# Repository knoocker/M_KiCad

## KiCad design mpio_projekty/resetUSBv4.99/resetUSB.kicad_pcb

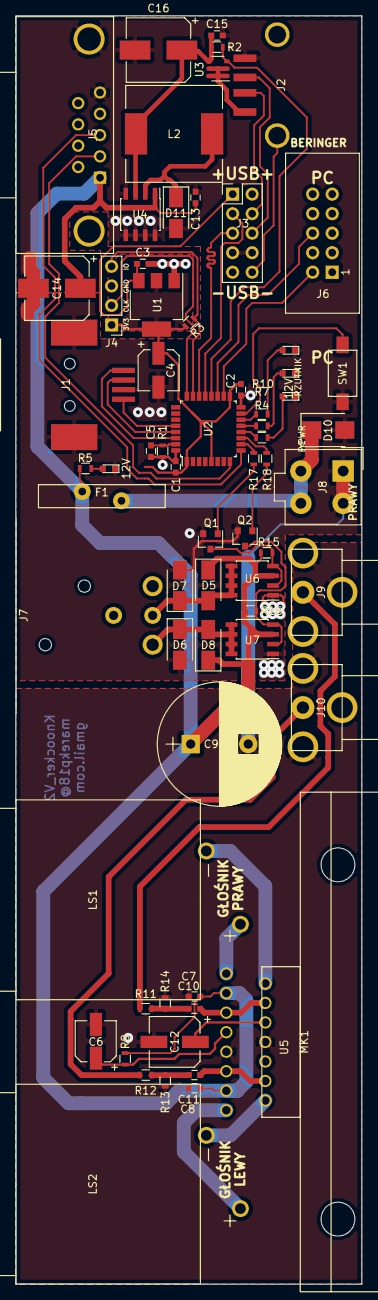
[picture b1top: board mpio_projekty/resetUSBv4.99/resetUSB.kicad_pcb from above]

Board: 2 copper layers, 45.0 x 165.0 mm, 67 parts (0 on the bottom side), 52 nets.

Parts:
C1, C2, C3, C5, C7, C8, C13, C15: 100n; C_0603
C4, C6: 10u; CP_Elec_5x5.3
C9: 4700u; CP_Radial_D16.0mm_P7.50mm
C10, C11: 0.47u; C_0603
C12: 47u; CP_Elec_6.3x5.3
C14, C16: 220u; CP_Elec_8x10.5
D1, D9: RED; LED_0603
D2: GREEN; LED_0603
D3: BLUE; LED_0603
D5, D6, D7, D8: US1D; D_SMA
D10: transil_15V; D_SMB
D11: SS14; D_SMA
F1: RG700-16; RG10A-16
J1: USBB-G-SMD; USB-B_SMD
J2: TUEA4F2SOBHT; USB-A_SMD
J3: Conn_02x05; Pin_Header_Straight_2x05_Pitch2.54mm
J4: SWD_4pin; Pin_Header_Straight_1x04_Pitch2.54mm
J5: DE09-SL-24; DSUB-9
J6: Conn_02x05; IDC10
J7: AC3MAH-AU-PRE
J8: Mini-Fit Jr; 4,2mm; Molex_MiniFit-JR-5556-04A_2x02x4.20mm_Straight
J9, J10: FC68391
L2: 47u; L_12x12mm_h6mm
LS1, LS2: NLJ2MD-H
MK1: SK48-50-SA-3
Q1, Q2: BC817; SOT-23
R1, R2, R3, R5: 100K; R_0603
R4: 22K; R_0603
R7: 6K8; R_0603
R9: 47K; R_0603
R10: 33K; R_0603
R11, R12: 4K7; R_0603
R13, R14, R15, R16, R17, R18: 10K; R_0603
SW1: TACTM-34N-F; SW_3x6_1,6x7,4
U1: LD1117S33TR; SOT-223-3_TabPin2
U2: STM32F042K6Tx; LQFP-32_7x7mm_Pitch0.8mm
U3: IRLTS2242; TSOP-6_1.65x3.05mm_Pitch0.95mm
U4: AP1509-50SG-13; SOIC-8_3.9x4.9mm_Pitch1.27mm
U5: TDA7375; MULTIWATT15
U6, U7: AO4616; SOIC-8_3.9x4.9mm_Pitch1.27mm

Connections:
+3V3: C1.1, C2.1, C4.1, J4.1, R3.2, U1.2, U2.1, U2.5, U2.17
+5P: C3.1, J3.1, U1.3
+5V: C15.1, C16.1, L2.2, R2.1, U3.4, U4.3
+12V: C7.1, C8.1, C9.1, C13.1, C14.1, D5.1, D6.1, F1.2, J5.1, R5.1, R9.1, R15.2, R16.2, U4.1, U5.3, U5.13, U6.3, U7.3
/LED_BLUE: R10.2, U2.14
/LED_GREEN: R7.2, U2.13
/LED_RED: R4.2, U2.12
/M_IN1: R17.2, U2.10
/M_IN2: R18.2, U2.11
/PC_LED: J6.2, U2.18
/PC_PWR: J6.6, U2.19
/PRZYCISK: SW1.2, U2.15
/RX: J5.3, U2.9
/RZUTNIK_DM: J1.2, U2.29
/RZUTNIK_DP: J1.3, U2.30
/RZUTNIK_VBUS: J1.1, U2.28
/SWCLK: J4.2, U2.24
/SWDIO: J4.4, R3.1, U2.23
/TX: J5.2, U2.8
/USB_DM: J3.3, U2.21
/USB_DP: J3.5, U2.22
/USB_PWR: R2.2, U2.20, U3.3
GND: C1.2, C2.2, C3.2, C4.2, C5.2, C6.2, C7.2, C8.2, C9.2, C12.2, C13.2, C14.2, C15.2, C16.2, D1.1, D2.1, D3.1, D7.2, D8.2, D9.1, D10.2, D11.2, J1.4, J1.5, J2.4, J3.7, J3.8, J4.3, J5.0, J5.5, J8.1, J8.2, J9.2, J10.2, Q1.2, Q2.2, R1.1, R13.2, R14.2, SW1.1, U1.1, U2.16, U2.32, U4.4, U4.5, U4.6, U4.7, U4.8, U5.8, U5.9, U6.1, U7.1
unnamed: C5.1, R1.2, U2.31
unnamed: C6.1, R9.2, U5.7
unnamed: C10.1, R11.2, R14.1
unnamed: C10.2, U5.4, U5.5
unnamed: C11.1, R12.2, R13.1
unnamed: C11.2, U5.11, U5.12
unnamed: C12.1, U5.6
unnamed: D1.2, R4.1
unnamed: D2.2, R7.1
unnamed: D3.2, R10.1
unnamed: D5.2, D7.1, J7.3, U6.5, U6.6, U6.7, U6.8
unnamed: D6.2, D8.1, J7.2, U7.5, U7.6, U7.7, U7.8
unnamed: D9.2, R5.2
unnamed: D10.1, F1.1, J8.3, J8.4
unnamed: D11.1, L2.1, U4.2
unnamed: J2.1, U3.1, U3.2, U3.5, U3.6
unnamed: J2.2, J3.4
unnamed: J2.3, J3.6
unnamed: J2.5, J3.10
unnamed: J9.1, R11.1
unnamed: J10.1, R12.1
unnamed: LS1.1, U5.1
unnamed: LS1.2, U5.2
unnamed: LS2.1, U5.15
unnamed: LS2.2, U5.14
unnamed: Q1.1, R17.1
unnamed: Q1.3, R15.1, U6.2, U6.4
unnamed: Q2.1, R18.1
unnamed: Q2.3, R16.1, U7.2, U7.4

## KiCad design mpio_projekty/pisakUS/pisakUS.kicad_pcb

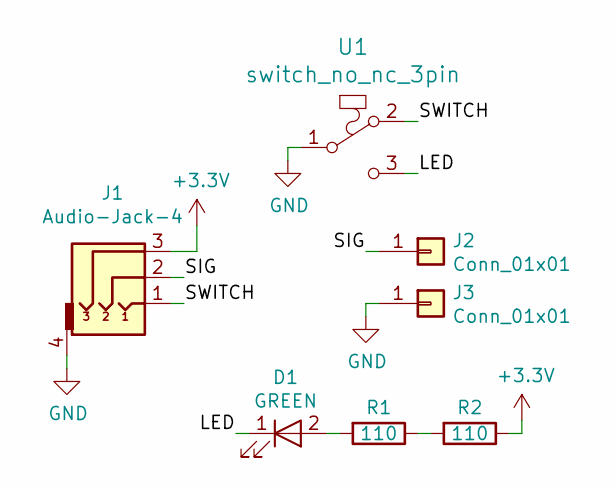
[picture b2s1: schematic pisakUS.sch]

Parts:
D1: GREEN; LED_0603
J1: Audio-Jack-4; 1503_13_VP3
J2, J3: Conn_01x01; Pin_Header_Straight_1x01_Pitch2.54mm
R1, R2: 110; R_0603
U1: switch_no_nc_3pin; D2FS-FL-N-T

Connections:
+3V3: J1.3, R2.1
/LED: D1.1 (K), U1.3
/SIG: J1.2, J2.1
/SWITCH: J1.1, U1.2
GND: J1.4, J3.1, U1.1
unnamed: D1.2 (A), R1.2
unnamed: R1.1, R2.2

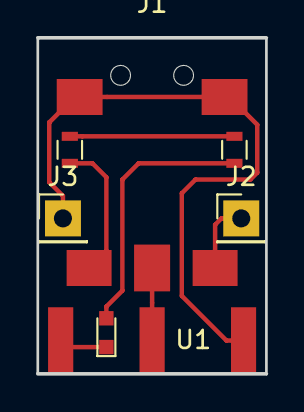
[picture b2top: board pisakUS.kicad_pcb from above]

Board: 2 copper layers, 12.7 x 18.7 mm, 7 parts (0 on the bottom side), 7 nets.

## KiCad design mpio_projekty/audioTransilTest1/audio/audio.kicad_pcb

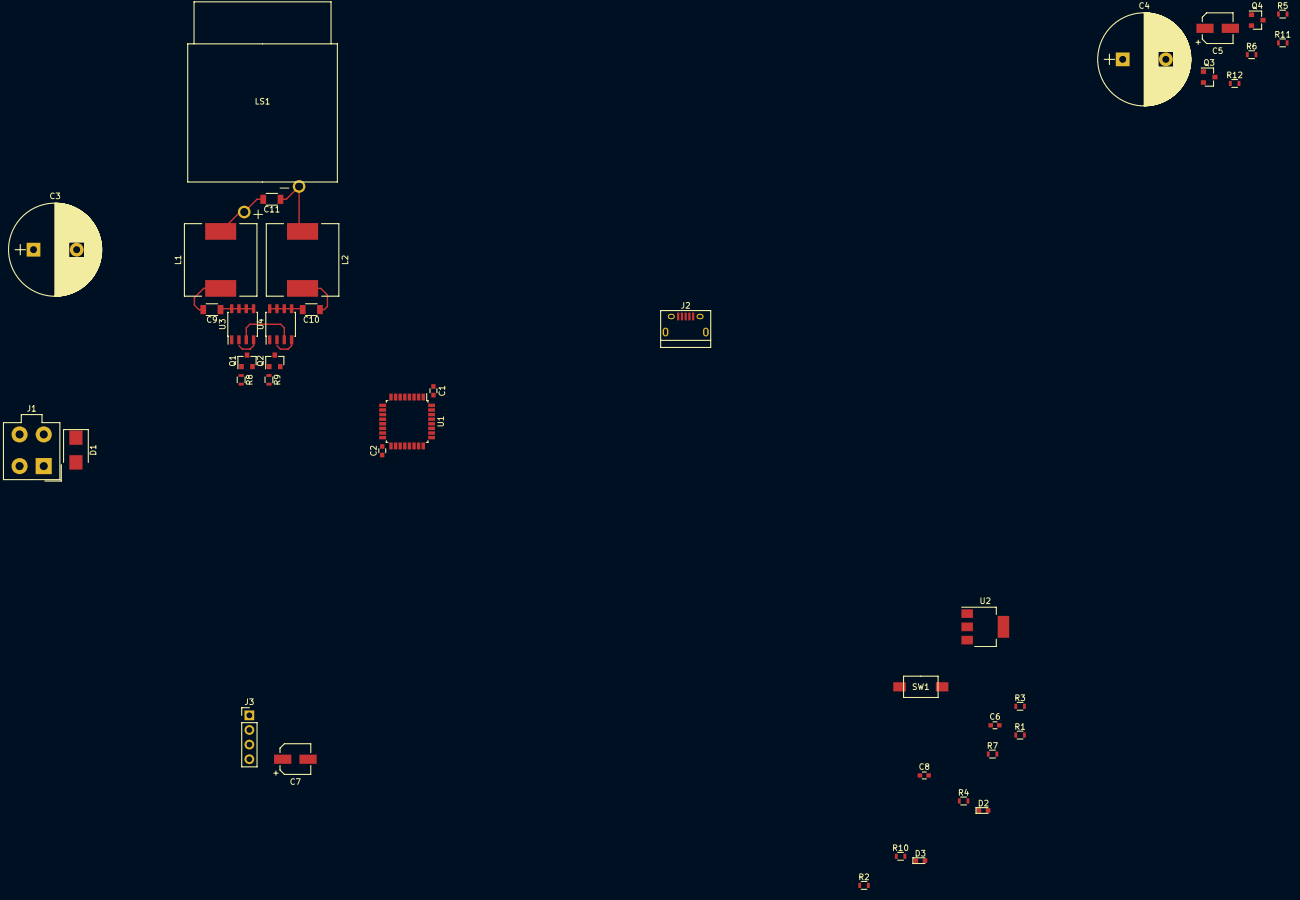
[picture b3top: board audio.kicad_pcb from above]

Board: 2 copper layers, 41 parts (0 on the bottom side), 29 nets.

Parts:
C1, C2, C6, C8: 100n; C_0603
C3: 4700u; CP_Radial_D16.0mm_P7.50mm
C4: 330u; CP_Radial_D16.0mm_P7.50mm
C5, C7: 10u; CP_Elec_5x5.3
C9, C10: 1u; C_1206
C11: 680n; C_1206
D1: transil_15V; D_SMB
D2, D3: RED; LED_0603
J1: Mini-Fit Jr; 4,2mm; Molex_MiniFit-JR-5556-04A_2x02x4.20mm_Straight
J2: USB_B; USB_Micro-B
J3: SWD_4pin; Pin_Header_Straight_1x04_Pitch2.54mm
L1, L2: 10/22u; L_12x12mm_h8mm
LS1: NLJ2MD-H
Q1, Q2, Q3, Q4: BC817; SOT-23
R1, R2, R3: 100K; R_0603
R4, R5, R6, R7, R8, R9, R11, R12: 10K; R_0603
R10: 22K; R_0603
SW1: TACTM-34N-F; SW_3x6_1,6x7,4
U1: STM32F042K6Tx; LQFP-32_7x7mm_Pitch0.8mm
U2: LD1117S33TR; SOT-223-3_TabPin2
U3, U4: AO4616; SOIC-8_3.9x4.9mm_Pitch1.27mm

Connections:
+3V3: C1.1, C2.1, C7.1, J3.1, R3.2, U1.1, U1.5, U1.17, U2.2
+5V: C5.1, C6.1, J2.1, U2.3
+12V: C3.1, C4.1, D1.1, J1.3, J1.4, R1.1, R4.2, R5.2, R6.2, R7.2, U3.3, U4.3
/SWCLK: J3.2, U1.24
/SWDIO: J3.4, R3.1, U1.23
/USB_M: J2.2, U1.21
/USB_P: J2.3, U1.22
/audio_1: R8.2, U1.18
/audio_1N: R11.2, U1.13
/audio_2: R9.2, U1.19
/audio_2N: R12.2, U1.14
GND: C1.2, C2.2, C3.2, C4.2, C5.2, C6.2, C7.2, C8.2, D1.2, D2.1, D3.1, J1.1, J1.2, J2.4, J2.5, J3.3, Q1.2, Q2.2, Q3.2, Q4.2, R2.1, SW1.1, U1.16, U1.32, U2.1, U3.1, U4.1
unnamed: C8.1, R2.2, U1.31
unnamed: C9.1, U3.5, U3.6, U3.7, U3.8
unnamed: C9.2, L1.1
unnamed: C10.1, L2.2
unnamed: C10.2, U4.5, U4.6, U4.7, U4.8
unnamed: C11.1, L2.1, LS1.2
unnamed: C11.2, L1.2, LS1.1
unnamed: D2.2, R1.2
unnamed: D3.2, R10.1
unnamed: Q1.1, R8.1
unnamed: Q1.3, R4.1, U3.4
unnamed: Q2.1, R9.1
unnamed: Q2.3, R7.1, U4.4
unnamed: Q3.1, R11.1
unnamed: Q3.3, R5.1, U3.2
unnamed: Q4.1, R12.1
unnamed: Q4.3, R6.1, U4.2

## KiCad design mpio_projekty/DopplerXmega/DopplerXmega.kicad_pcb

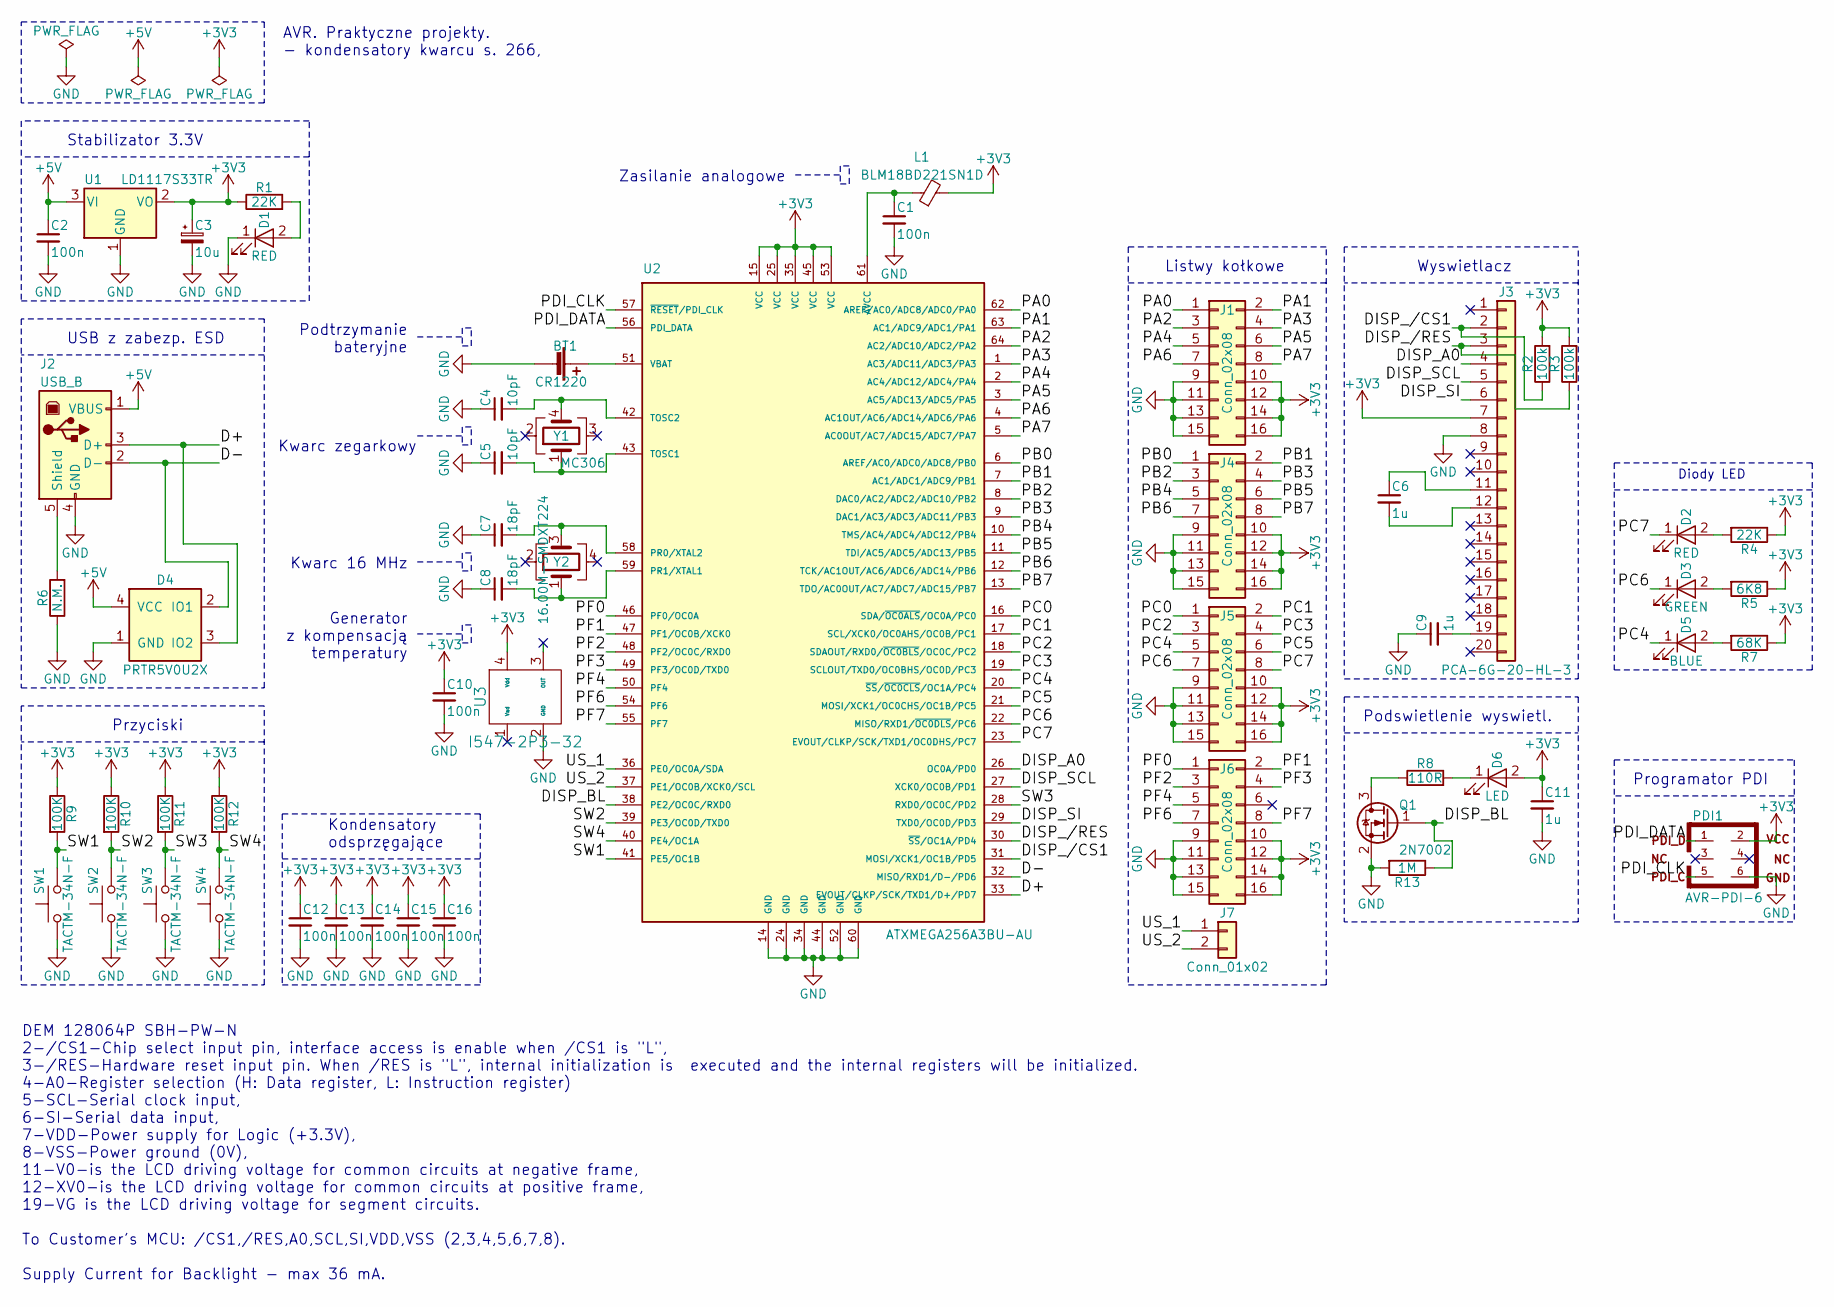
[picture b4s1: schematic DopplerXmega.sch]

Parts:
BT1: CR1220; Keystone_3000_1x12mm-CoinCell
C1, C2, C10, C12, C13, C14, C15, C16: 100n; C_0603
C3: 10u; CP_Elec_5x5.3
C4, C5: 10pF; C_0603
C6, C9, C11: 1u; C_0603
C7, C8: 18pF; C_0603
D1, D2: RED; LED_0603
D3: GREEN; LED_0603
D4: PRTR5V0U2X; SOT-143
D5: BLUE; LED_0603
D6: LED; DEM_128064P_SBH-PW-N
J1, J4, J5, J6: Conn_02x08; Pin_Header_Straight_2x08_Pitch2.54mm
J2: USB_B; USB_Micro-B
J3: PCA-6G-20-HL-3
J7: Conn_01x02; Pin_Header_Straight_1x02_Pitch2.54mm
L1: BLM18BD221SN1D; L_0603
PDI1: AVR-PDI-6; Pin_Header_Straight_2x03_Pitch2.54mm
Q1: 2N7002; SOT-23
R1, R4: 22K; R_0603
R2, R3: 100k; R_0603
R5: 6K8; R_0603
R6: N.M.; R_0603
R7: 68K; R_0603
R8: 110R; R_0603
R9, R10, R11, R12: 100K; R_0603
R13: 1M; R_0603
SW1, SW2, SW3, SW4: TACTM-34N-F; SW_3x6_1,6x7,4
U1: LD1117S33TR; SOT-223-3_TabPin2
U2: ATXMEGA256A3BU-AU; TQFP-64_14x14mm_Pitch0.8mm
U3: I547-2P3-32; crystal_3.2x2.5
Y1: MC306; Crystal_SMD_SeikoEpson_MC306-4pin_8.0x3.2mm
Y2: 16.00M-SMDXT224; Crystal_SMD_2520-4pin_2.5x2.0mm

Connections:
+3V3: C3.1, C10.1, C11.1, C12.1, C13.1, C14.1, C15.1, C16.1, D6.2 (A), J1.10, J1.12, J1.14, J1.16, J3.7, J4.10, J4.12, J4.14, J4.16, J5.10, J5.12, J5.14, J5.16, J6.10, J6.12, J6.14, J6.16, L1.2, PDI1.2, R1.1, R2.2, R3.2, R4.1, R5.1, R7.1, R9.1, R10.1, R11.1, R12.1, U1.2 (VO), U2.15 (VCC), U2.25 (VCC), U2.35 (VCC), U2.45 (VCC), U2.53 (VCC), U3.4 (Vdd)
+5V: C2.1, D4.4 (VCC), J2.1 (VBUS), U1.3 (VI)
/D+: D4.3 (IO2), J2.3 (D+), U2.33 (EVOUT/CLKP/SCK/TXD1/D+/PD7)
/D-: D4.2 (IO1), J2.2 (D-), U2.32 (MISO/RXD1/D-/PD6)
/DISP_/CS1: J3.2, R2.1, U2.31 (MOSI/XCK1/OC1B/PD5)
/DISP_/RES: J3.3, R3.1, U2.30 (~SS~/OC1A/PD4)
/DISP_A0: J3.4, U2.26 (OC0A/PD0)
/DISP_BL: Q1.1 (G), R13.1, U2.38 (PE2/OC0C/RXD0)
/DISP_SCL: J3.5, U2.27 (XCK0/OC0B/PD1)
/DISP_SI: J3.6, U2.29 (TXD0/OC0D/PD3)
/PA0: J1.1, U2.62 (AREF/AC0/ADC8/ADC0/PA0)
/PA1: J1.2, U2.63 (AC1/ADC9/ADC1/PA1)
/PA2: J1.3, U2.64 (AC2/ADC10/ADC2/PA2)
/PA3: J1.4, U2.1 (AC3/ADC11/ADC3/PA3)
/PA4: J1.5, U2.2 (AC4/ADC12/ADC4/PA4)
/PA5: J1.6, U2.3 (AC5/ADC13/ADC5/PA5)
/PA6: J1.7, U2.4 (AC1OUT/AC6/ADC14/ADC6/PA6)
/PA7: J1.8, U2.5 (AC0OUT/AC7/ADC15/ADC7/PA7)
/PB0: J4.1, U2.6 (AREF/AC0/ADC0/ADC8/PB0)
/PB1: J4.2, U2.7 (AC1/ADC1/ADC9/PB1)
/PB2: J4.3, U2.8 (DAC0/AC2/ADC2/ADC10/PB2)
/PB3: J4.4, U2.9 (DAC1/AC3/ADC3/ADC11/PB3)
/PB4: J4.5, U2.10 (TMS/AC4/ADC4/ADC12/PB4)
/PB5: J4.6, U2.11 (TDI/AC5/ADC5/ADC13/PB5)
/PB6: J4.7, U2.12 (TCK/AC1OUT/AC6/ADC6/ADC14/PB6)
/PB7: J4.8, U2.13 (TDO/AC0OUT/AC7/ADC7/ADC15/PB7)
/PC0: J5.1, U2.16 (SDA/~OC0ALS~/OC0A/PC0)
/PC1: J5.2, U2.17 (SCL/XCK0/OC0AHS/OC0B/PC1)
/PC2: J5.3, U2.18 (SDAOUT/RXD0/~OC0BLS~/OC0C/PC2)
/PC3: J5.4, U2.19 (SCLOUT/TXD0/OC0BHS/OC0D/PC3)
/PC4: D5.1 (K), J5.5, U2.20 (~SS~/~OC0CLS~/OC1A/PC4)
/PC5: J5.6, U2.21 (MOSI/XCK1/OC0CHS/OC1B/PC5)
/PC6: D3.1 (K), J5.7, U2.22 (MISO/RXD1/~OC0DLS~/PC6)
/PC7: D2.1 (K), J5.8, U2.23 (EVOUT/CLKP/SCK/TXD1/OC0DHS/PC7)
/PDI_CLK: PDI1.5, U2.57 (~RESET~/PDI_CLK)
/PDI_DATA: PDI1.1, U2.56 (PDI_DATA)
/PF0: J6.1, U2.46 (PF0/OC0A)
/PF1: J6.2, U2.47 (PF1/OC0B/XCK0)
/PF2: J6.3, U2.48 (PF2/OC0C/RXD0)
/PF3: J6.4, U2.49 (PF3/OC0D/TXD0)
/PF4: J6.5, U2.50 (PF4)
/PF6: J6.7, U2.54 (PF6)
/PF7: J6.8, U2.55 (PF7)
/SW1: R9.2, SW1.2, U2.41 (PE5/OC1B)
/SW2: R10.2, SW2.2, U2.39 (PE3/OC0D/TXD0)
/SW3: R11.2, SW3.2, U2.28 (RXD0/OC0C/PD2)
/SW4: R12.2, SW4.2, U2.40 (PE4/OC1A)
/US_1: J7.1, U2.36 (PE0/OC0A/SDA)
/US_2: J7.2, U2.37 (PE1/OC0B/XCK0/SCL)
GND: BT1.2 (-), C1.2, C2.2, C3.2, C4.1, C5.1, C7.1, C8.1, C9.1, C10.2, C11.2, C12.2, C13.2, C14.2, C15.2, C16.2, D1.1 (K), D4.1 (GND), J1.9, J1.11, J1.13, J1.15, J2.4 (GND), J3.8, J4.9, J4.11, J4.13, J4.15, J5.9, J5.11, J5.13, J5.15, J6.9, J6.11, J6.13, J6.15, PDI1.6, Q1.2 (S), R6.1, R13.2, SW1.1, SW2.1, SW3.1, SW4.1, U1.1 (GND), U2.14 (GND), U2.24 (GND), U2.34 (GND), U2.44 (GND), U2.52 (GND), U2.60 (GND), U3.2 (GND)
unnamed: BT1.1 (+), U2.51 (VBAT)
unnamed: C1.1, L1.1, U2.61 (AVCC)
unnamed: C4.2, U2.42 (TOSC2), Y1.4
unnamed: C5.2, U2.43 (TOSC1), Y1.1
unnamed: C6.1, J3.11
unnamed: C6.2, J3.12
unnamed: C7.2, U2.58 (PR0/XTAL2), Y2.3
unnamed: C8.2, U2.59 (PR1/XTAL1), Y2.1
unnamed: C9.2, J3.19
unnamed: D1.2 (A), R1.2
unnamed: D2.2 (A), R4.2
unnamed: D3.2 (A), R5.2
unnamed: D5.2 (A), R7.2
unnamed: D6.1 (K), R8.2
unnamed: J2.5 (Shield), R6.2
unnamed: Q1.3 (D), R8.1

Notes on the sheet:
AVR. Praktyczne projekty. - kondensatory kwarcu s. 266,
Kondensatory odsprzęgające
DEM 128064P SBH-PW-N 2-/CS1-Chip select input pin, interface access is enable when /CS1 is "L", 3-/RES-Hardware reset input pin. When /RES is "L", internal initialization is executed and the internal registers will be initialized. 4-A0-Register selection (H: Data register, L: Instruction register) 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
Programator PDI
Podswietlenie wyswietl.
Wyswietlacz
Listwy kołkowe
Przyciski
USB z zabezp. ESD
Stabilizator 3.3V
Podtrzymanie bateryjne
Kwarc zegarkowy
Kwarc 16 MHz
Generator z kompensacją temperatury
Zasilanie analogowe
Diody LED

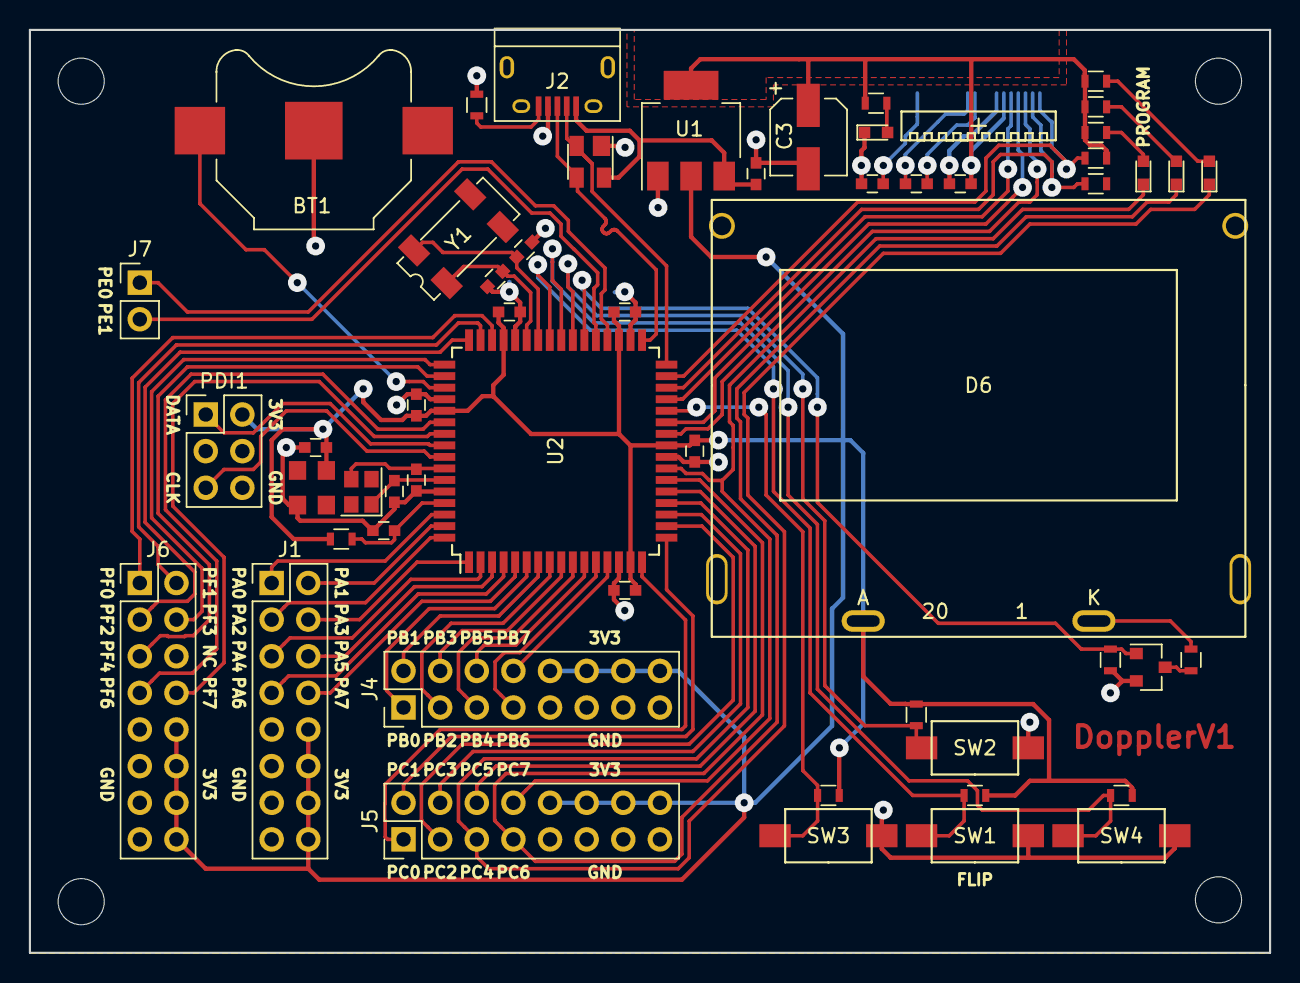
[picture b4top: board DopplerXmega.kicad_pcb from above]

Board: 2 copper layers, 86.0 x 64.0 mm, 55 parts (1 on the bottom side), 66 nets.

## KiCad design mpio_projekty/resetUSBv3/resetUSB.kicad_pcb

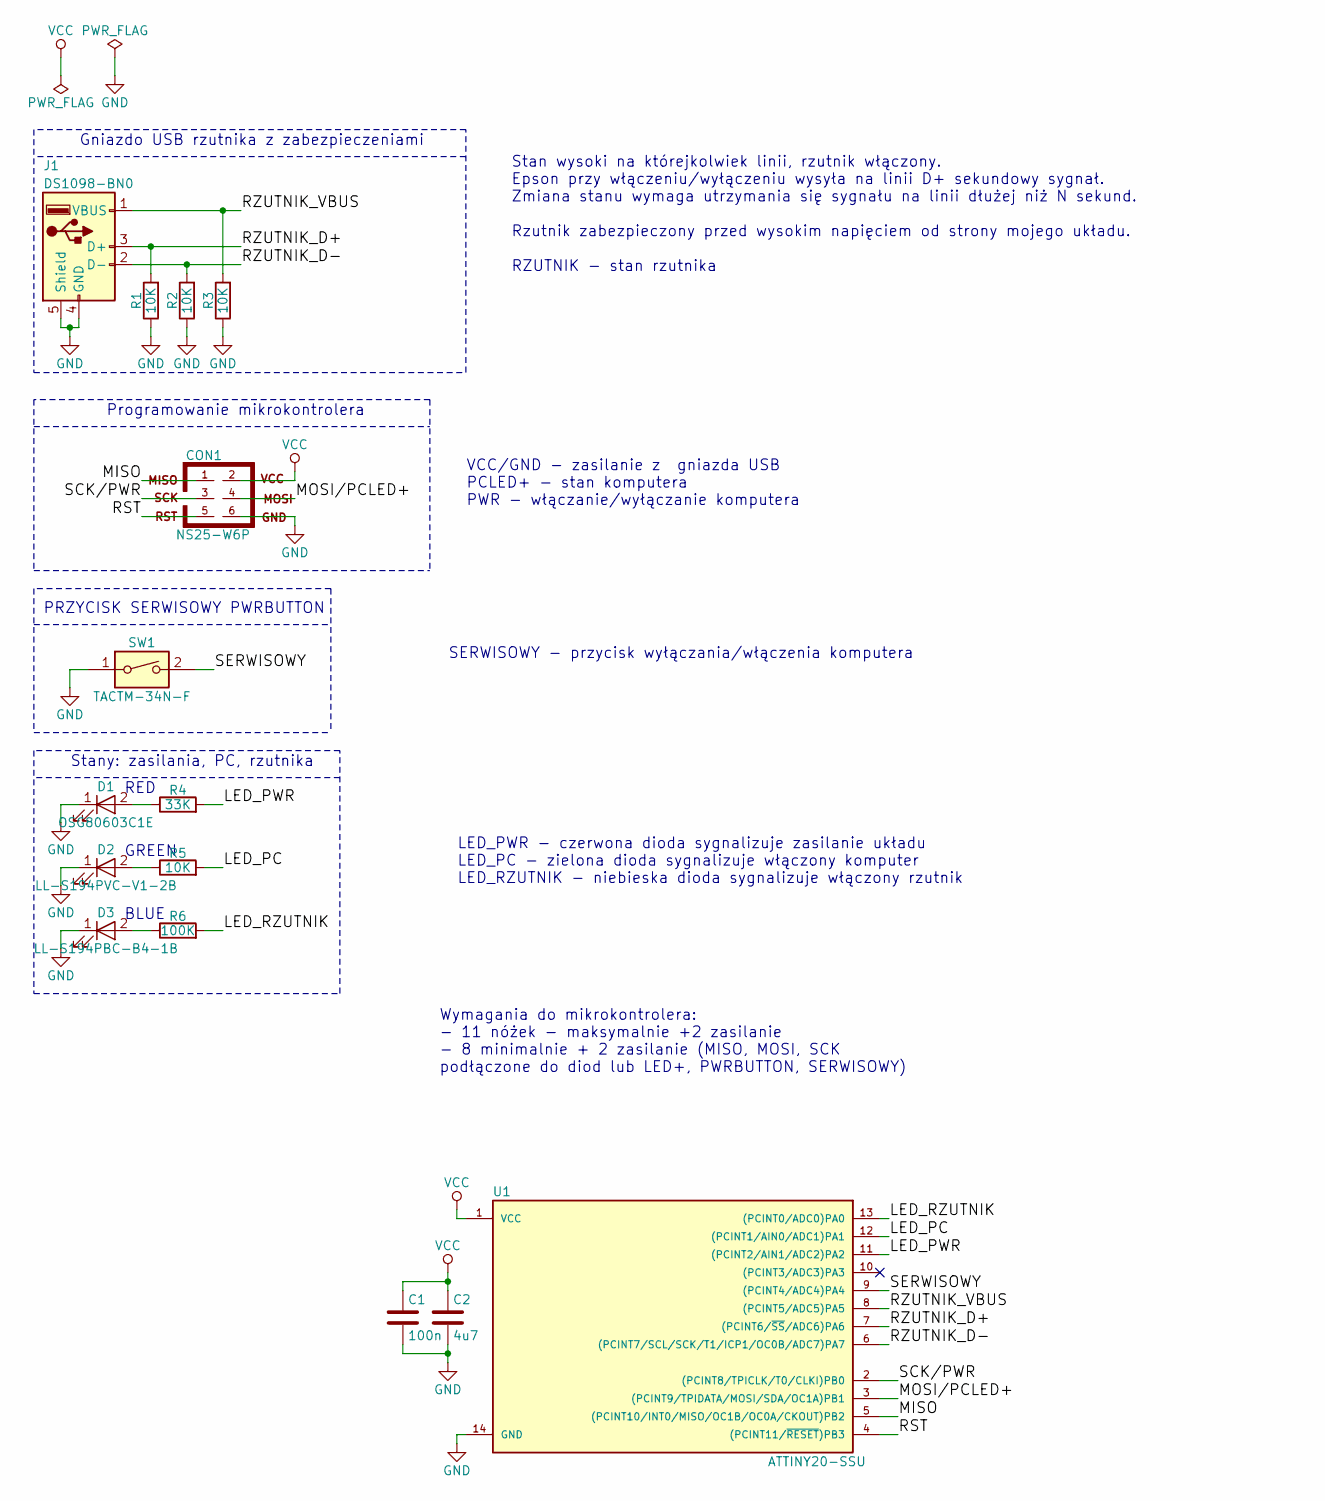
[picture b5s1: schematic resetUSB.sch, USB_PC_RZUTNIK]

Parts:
C1: 100n; C_0805
C2: 4u7; C_0603
CON1: NS25-W6P
D1: OSG80603C1E; LED_0603
D2: LL-S194PVC-V1-2B; LED_0603
D3: LL-S194PBC-B4-1B; LED_0603
J1: DS1098-BN0; USB_A_CONNFLY_DS1098
R1, R2, R3, R5: 10K; R_0603
R4: 33K; R_0603
R6: 100K; R_0603
SW1: TACTM-34N-F; SW_3x6_1,6x7,4
U1: ATTINY20-SSU; SOIC-14_3.9x8.7mm_Pitch1.27mm

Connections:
/LED_PC: R5.2, U1.12 ((PCINT1/AIN0/ADC1)PA1)
/LED_PWR: R4.2, U1.11 ((PCINT2/AIN1/ADC2)PA2)
/LED_RZUTNIK: R6.2, U1.13 ((PCINT0/ADC0)PA0)
/MISO: CON1.1, U1.5 ((PCINT10/INT0/MISO/OC1B/OC0A/CKOUT)PB2)
/MOSI/PCLED+: CON1.4, U1.3 ((PCINT9/TPIDATA/MOSI/SDA/OC1A)PB1)
/RST: CON1.5, U1.4 ((PCINT11/~RESET~)PB3)
/RZUTNIK_D+: J1.3 (D+), R1.2, U1.7 ((PCINT6/~SS~/ADC6)PA6)
/RZUTNIK_D-: J1.2 (D-), R2.2, U1.6 ((PCINT7/SCL/SCK/T1/ICP1/OC0B/ADC7)PA7)
/RZUTNIK_VBUS: J1.1 (VBUS), R3.2, U1.8 ((PCINT5/ADC5)PA5)
/SCK/PWR: CON1.3, U1.2 ((PCINT8/TPICLK/T0/CLKI)PB0)
/SERWISOWY: SW1.2, U1.9 ((PCINT4/ADC4)PA4)
GND: C1.2, C2.2, CON1.6, D1.1 (K), D2.1 (K), D3.1 (K), J1.4 (GND), J1.5 (Shield), R1.1, R2.1, R3.1, SW1.1, U1.14 (GND)
unnamed: D1.2 (A), R4.1
unnamed: D2.2 (A), R5.1
unnamed: D3.2 (A), R6.1
VCC: C1.1, C2.1, CON1.2, U1.1 (VCC)

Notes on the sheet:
Gniazdo USB rzutnika z zabezpieczeniami
Stan wysoki na którejkolwiek linii, rzutnik włączony. Epson przy włączeniu/wyłączeniu wysyła na linii D+ sekundowy sygnał. Zmiana stanu wymaga utrzymania się sygnału na linii dłużej niż N sekund. Rzutnik zabezpieczony przed wysokim napięciem od strony mojego układu. RZUTNIK - stan rzutnika
VCC/GND - zasilanie z gniazda USB PCLED+ - stan komputera PWR - włączanie/wyłączanie komputera
PRZYCISK SERWISOWY PWRBUTTON
Stany: zasilania, PC, rzutnika
SERWISOWY - przycisk wyłączania/włączenia komputera
LED_PWR - czerwona dioda sygnalizuje zasilanie układu LED_PC - zielona dioda sygnalizuje włączony komputer LED_RZUTNIK - niebieska dioda sygnalizuje włączony rzutnik
Wymagania do mikrokontrolera: - 11 nóżek - maksymalnie +2 zasilanie - 8 minimalnie + 2 zasilanie (MISO, MOSI, SCK podłączone do diod lub LED+, PWRBUTTON, SERWISOWY)
Programowanie mikrokontrolera
RED
GREEN
BLUE

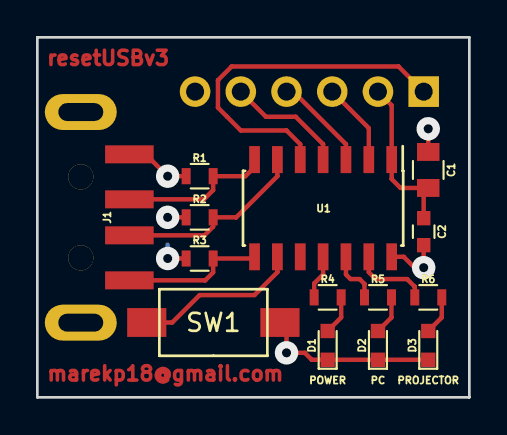
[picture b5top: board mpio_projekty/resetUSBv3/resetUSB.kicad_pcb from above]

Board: 2 copper layers, 24.0 x 20.0 mm, 15 parts (1 on the bottom side), 16 nets.

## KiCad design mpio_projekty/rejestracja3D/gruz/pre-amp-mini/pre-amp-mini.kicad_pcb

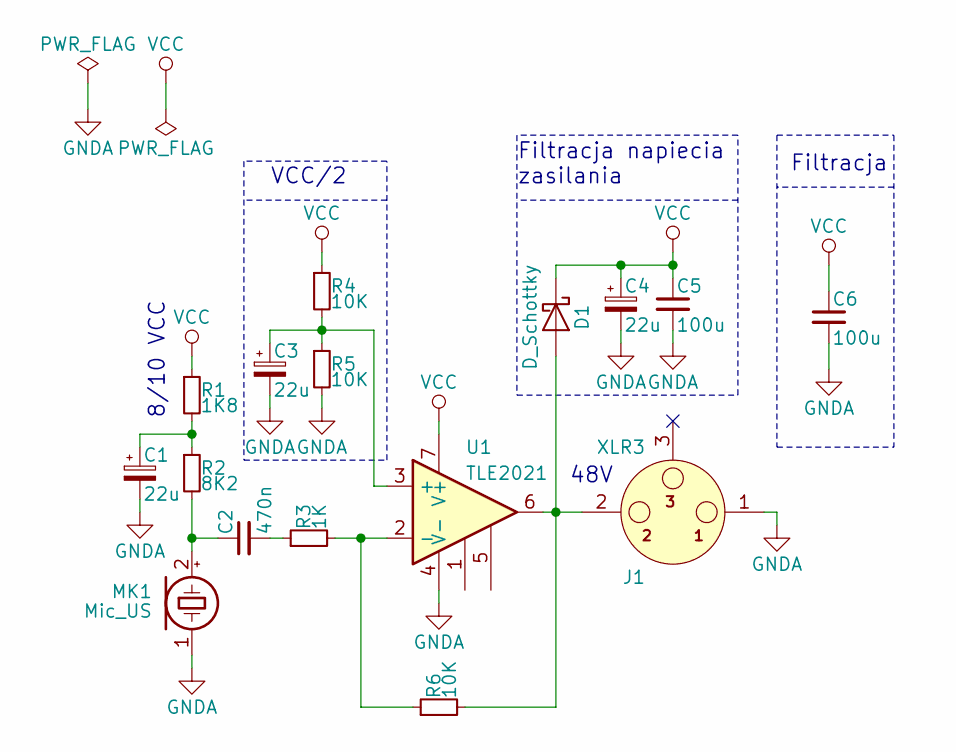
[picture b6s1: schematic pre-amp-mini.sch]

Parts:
C1, C3, C4: 22u; CP_Elec_4x4.5
C2: 470n; C_0603
C5, C6: 100u; C_0603
D1: D_Schottky; D_0603
J1: XLR3; XLR-3
MK1: Mic_US; Pin_Header_Straight_1x02_Pitch2.54mm
R1: 1K8; R_0603
R2: 8K2; R_0603
R3: 1K; R_0603
R4, R5, R6: 10K; R_0603
U1: TLE2021; SOIC-8_3.9x4.9mm_Pitch1.27mm

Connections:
GNDA: C1.2, C3.2, C4.2, C5.2, C6.2, J1.1, MK1.1 (-), R5.2, U1.4 (V-)
unnamed: C1.1, R1.2, R2.1
unnamed: C2.1, MK1.2 (+), R2.2
unnamed: C2.2, R3.1
unnamed: C3.1, R4.2, R5.1, U1.3 (+)
unnamed: D1.2 (A), J1.2, R6.2, U1.6
unnamed: R3.2, R6.1, U1.2 (-)
VCC: C4.1, C5.1, C6.1, D1.1 (K), R1.1, R4.1, U1.7 (V+)

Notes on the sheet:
Filtracja
48V
VCC/2
8/10 VCC
Filtracja napiecia zasilania

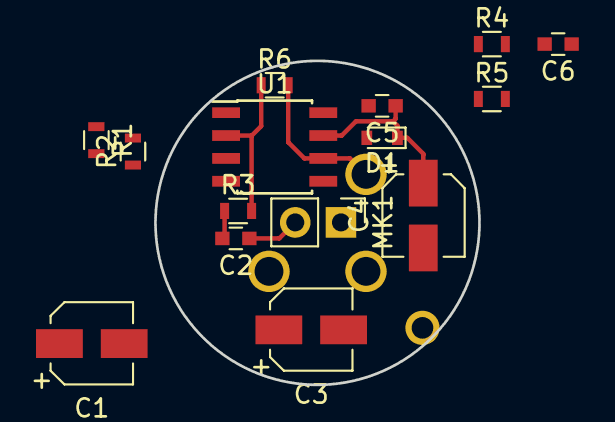
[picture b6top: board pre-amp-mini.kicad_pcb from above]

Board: 2 copper layers, 18.0 x 18.0 mm, 16 parts (1 on the bottom side), 8 nets.

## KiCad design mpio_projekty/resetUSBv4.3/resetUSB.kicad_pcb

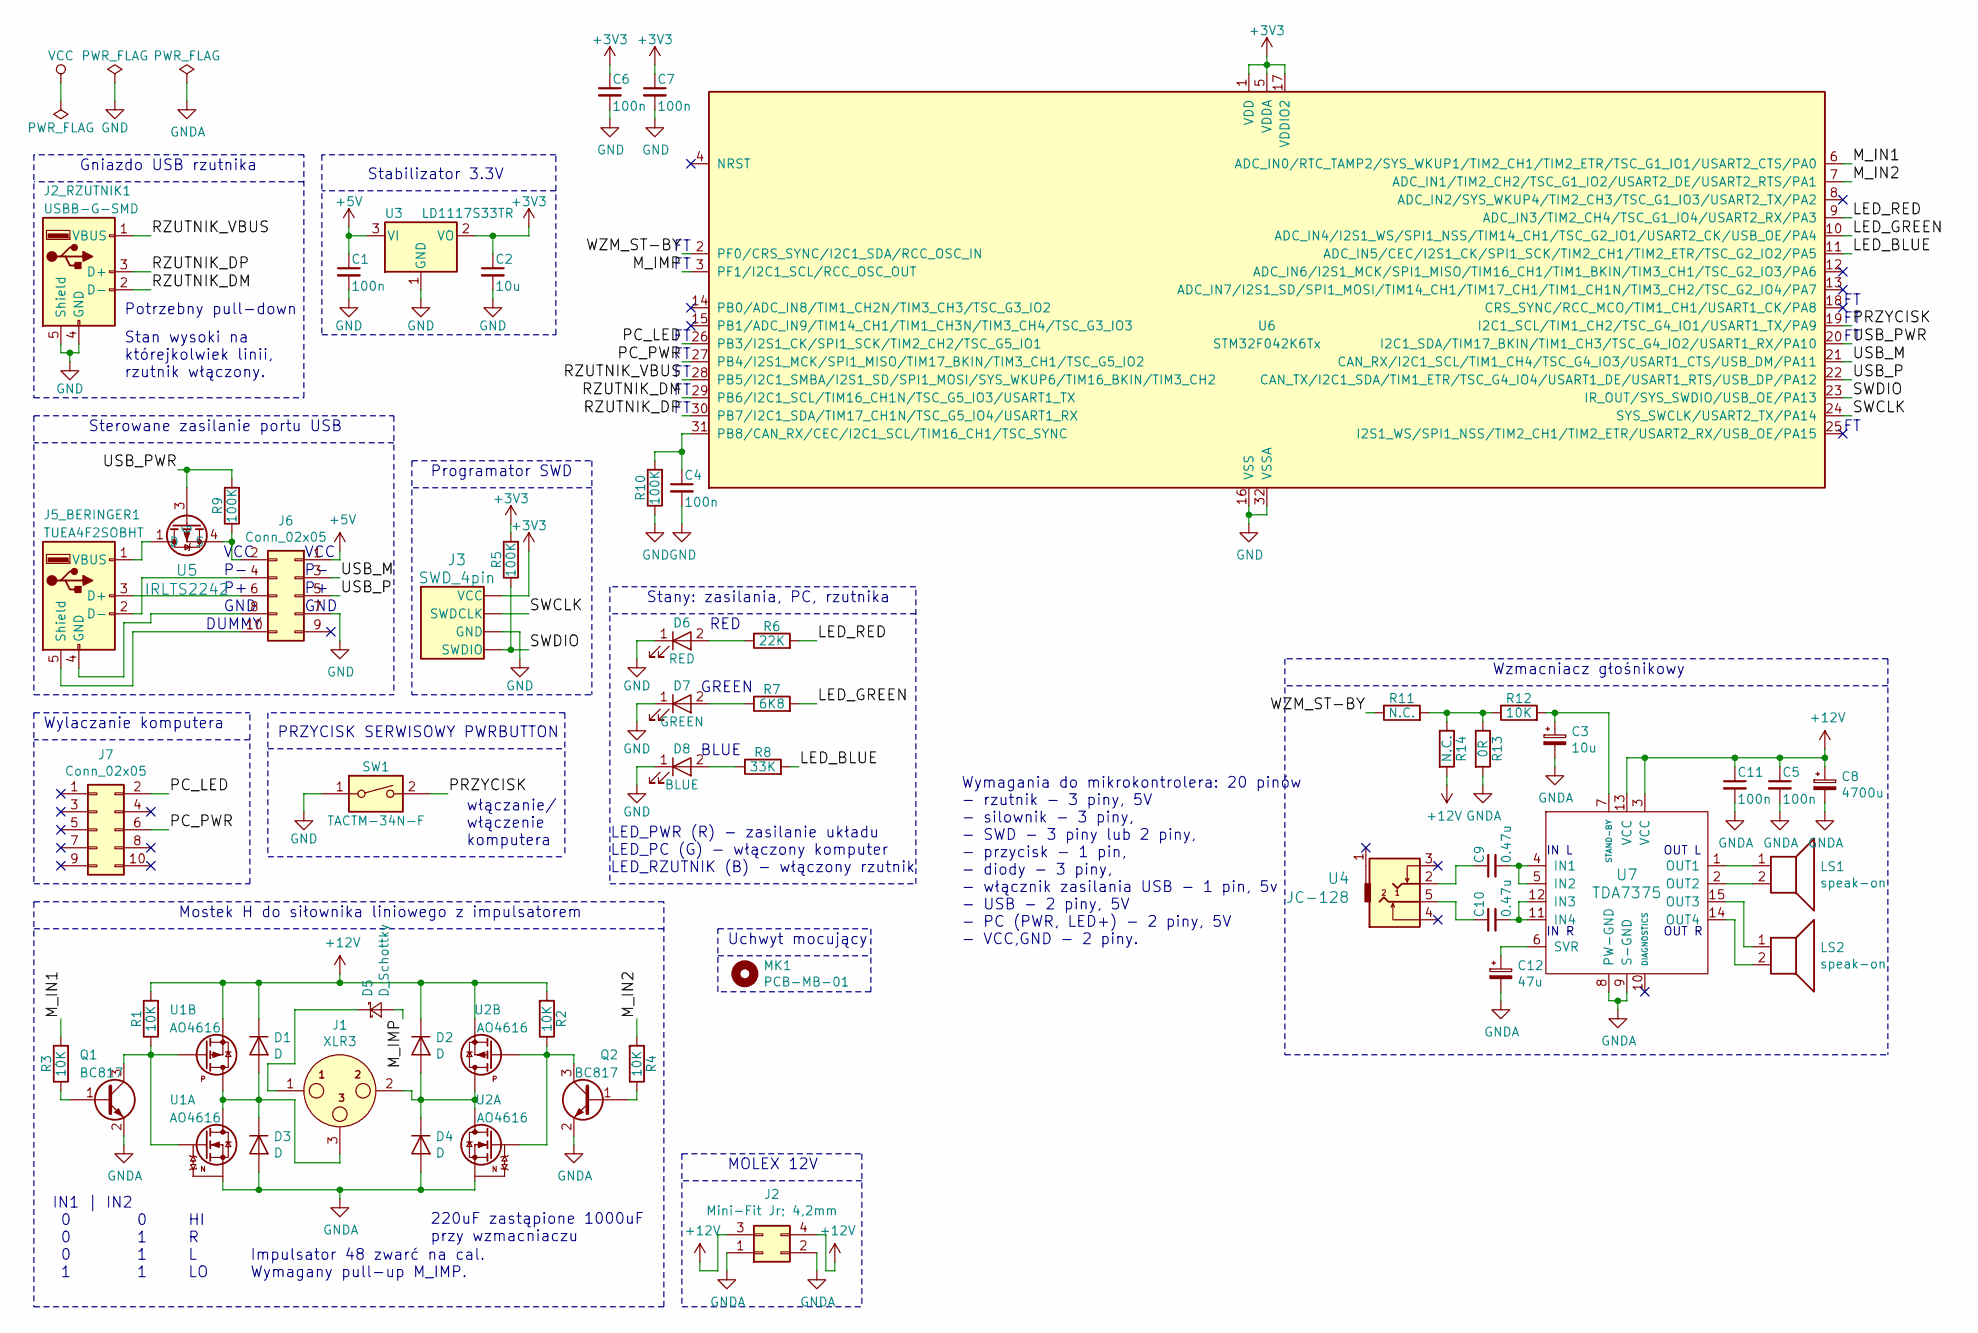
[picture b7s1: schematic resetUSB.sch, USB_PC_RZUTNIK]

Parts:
C1, C4, C5, C6, C7, C11: 100n; C_0603
C2, C3: 10u; CP_Elec_5x5.3
C8: 4700u; CP_Radial_D16.0mm_P7.50mm
C9, C10: 0.47u; C_0603
C12: 47u; CP_Elec_5x5.3
D1, D2, D3, D4: D; D_SMA
D5: D_Schottky; D_SOD-523
D6: RED; LED_0603
D7: GREEN; LED_0603
D8: BLUE; LED_0603
J1: XLR3; AC3MAH-AU-PRE
J2: Mini-Fit Jr; 4,2mm; Molex_MiniFit-JR-5556-04A_2x02x4.20mm_Straight
J2_RZUTNIK1: USBB-G-SMD; USB-B_SMD
J3: SWD_4pin; Pin_Header_Straight_1x04_Pitch2.54mm
J5_BERINGER1: TUEA4F2SOBHT; USB-A_SMD
J6, J7: Conn_02x05; IDC10
LS1, LS2: speak-on; NLJ2MD-H
MK1: PCB-MB-01
Q1, Q2: BC817; SOT-23
R1, R2, R3, R4, R12: 10K; R_0603
R5, R9, R10: 100K; R_0603
R6: 22K; R_0603
R7: 6K8; R_0603
R8: 33K; R_0603
R11, R14: N.C.; R_0603
R13: 0R; R_0603
SW1: TACTM-34N-F; SW_3x6_1,6x7,4
U1, U2: AO4616; SOIC-8_3.9x4.9mm_Pitch1.27mm
U3: LD1117S33TR; SOT-223-3_TabPin2
U4: JC-128
U5: IRLTS2242; TSOP-6_1.65x3.05mm_Pitch0.95mm
U6: STM32F042K6Tx; LQFP-32_5x5mm_Pitch0.5mm
U7: TDA7375; MULTIWATT15

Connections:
+3V3: C2.1, C6.1, C7.1, J3.1 (VCC), R5.2, U3.2 (VO), U6.1 (VDD), U6.5 (VDDA), U6.17 (VDDIO2)
+5V: C1.1, J6.1, U3.3 (VI)
+12V: C5.1, C8.1, C11.1, D1.1 (K), D2.1 (K), J2.3, J2.4, R1.2, R2.2, R14.2, U1.3 (S), U2.3 (S), U7.3 (VCC), U7.13 (VCC)
/LED_BLUE: R8.2, U6.11 (ADC_IN5/CEC/I2S1_CK/SPI1_SCK/TIM2_CH1/T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)
/LED_GREEN: R7.2, U6.10 (ADC_IN4/I2S1_WS/SPI1_NSS/TIM14_CH1/TSC_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)
/LED_RED: R6.2, U6.9 (ADC_IN3/TIM2_CH4/TSC_G1_IO4/USART2_RX/P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)
/M_IMP: D5.2 (A), U6.3 (PF1/I2C1_SCL/RCC_OSC_OUT)
/M_IN1: R3.2, U6.6 (ADC_IN0/RTC_TAMP2/SYS_WKUP1/TIM2_CH1/TI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)
/M_IN2: R4.2, U6.7 (ADC_IN1/TIM2_CH2/TSC_G1_IO2/USART2_DE/U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)
/PC_LED: J7.2, U6.26 (PB3/I2S1_CK/SPI1_SCK/TIM2_CH2/TSC_G5_IO1)
/PC_PWR: J7.6, U6.27 (PB4/I2S1_MCK/SPI1_MISO/TIM17_BKIN/TIM3_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)
/PRZYCISK: SW1.2, U6.19 (I2C1_SCL/TIM1_CH2/TSC_G4_IO1/USART1_TX/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)
/RZUTNIK_DM: J2_RZUTNIK1.2 (D-), U6.29 (PB6/I2C1_SCL/TIM16_CH1N/TSC_G5_IO3/USAR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)
/RZUTNIK_DP: J2_RZUTNIK1.3 (D+), U6.30 (PB7/I2C1_SDA/TIM17_CH1N/TSC_G5_IO4/USAR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)
/RZUTNIK_VBUS: J2_RZUTNIK1.1 (VBUS), U6.28 (PB5/I2C1_SMBA/I2S1_SD/SPI1_MOSI/SYS_WKU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)
/SWCLK: J3.2 (SWDCLK), U6.24 (SYS_SWCLK/USART2_TX/PA14)
/SWDIO: J3.4 (SWDIO), R5.1, U6.23 (IR_OUT/SYS_SWDIO/USB_OE/PA13)
/USB_M: J6.3, U6.21 (CAN_RX/I2C1_SCL/TIM1_CH4/TSC_G4_IO3/USA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)
/USB_P: J6.5, U6.22 (CAN_TX/I2C1_SDA/TIM1_ETR/TSC_G4_IO4/USA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)
/USB_PWR: R9.2, U5.3 (G), U6.20 (I2C1_SDA/TIM17_BKIN/TIM1_CH3/TSC_G4_IO2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)
/WZM_ST-BY: R11.1, U6.2 (PF0/CRS_SYNC/I2C1_SDA/RCC_OSC_IN)
GND: C1.2, C2.2, C4.2, C6.2, C7.2, D6.1 (K), D7.1 (K), D8.1 (K), J2_RZUTNIK1.4 (GND), J2_RZUTNIK1.5 (Shield), J3.3 (GND), J6.7, R10.1, SW1.1, U3.1 (GND), U6.16 (VSS), U6.32 (VSSA)
GNDA: C3.2, C5.2, C8.2, C11.2, C12.2, D3.2 (A), D4.2 (A), J2.1, J2.2, Q1.2 (E), Q2.2 (E), R13.2, U1.1 (S), U2.1 (S), U7.8 (PW-GND), U7.9 (S-GND)
unnamed: C3.1, R12.2, U7.7 (STAND-BY)
unnamed: C4.1, R10.2, U6.31 (PB8/CAN_RX/CEC/I2C1_SCL/TIM16_CH1/TSC_S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)
unnamed: C9.1, U4.2
unnamed: C9.2, U7.4 (IN1), U7.5 (IN2)
unnamed: C10.1, U4.5
unnamed: C10.2, U7.11 (IN4), U7.12 (IN3)
unnamed: C12.1, U7.6 (SVR)
unnamed: D1.2 (A), D3.1 (K), J1.3, U1.5 (D), U1.6 (D), U1.7 (D), U1.8 (D)
unnamed: D2.2 (A), D4.1 (K), J1.2, U2.5 (D), U2.6 (D), U2.7 (D), U2.8 (D)
unnamed: D5.1 (K), J1.1
unnamed: D6.2 (A), R6.1
unnamed: D7.2 (A), R7.1
unnamed: D8.2 (A), R8.1
unnamed: J5_BERINGER1.1 (VBUS), U5.1 (D), U5.2 (D), U5.5 (D), U5.6 (D)
unnamed: J5_BERINGER1.2 (D-), J6.4
unnamed: J5_BERINGER1.3 (D+), J6.6
unnamed: J5_BERINGER1.4 (GND), J6.8
unnamed: J5_BERINGER1.5 (Shield), J6.10
unnamed: J6.2, R9.1, U5.4 (S)
unnamed: LS1.1, U7.1 (OUT1)
unnamed: LS1.2, U7.2 (OUT2)
unnamed: LS2.1, U7.15 (OUT3)
unnamed: LS2.2, U7.14 (OUT4)
unnamed: Q1.1 (B), R3.1
unnamed: Q1.3 (C), R1.1, U1.2 (G), U1.4 (G)
unnamed: Q2.1 (B), R4.1
unnamed: Q2.3 (C), R2.1, U2.2 (G), U2.4 (G)
unnamed: R11.2, R12.1, R13.1, R14.1

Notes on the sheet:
Gniazdo USB rzutnika
Stan wysoki na którejkolwiek linii, rzutnik włączony.
PRZYCISK SERWISOWY PWRBUTTON
Stany: zasilania, PC, rzutnika
włączanie/ włączenie komputera
LED_PWR (R) - zasilanie układu LED_PC (G) - włączony komputer LED_RZUTNIK (B) - włączony rzutnik
Wymagania do mikrokontrolera: 20 pinów - rzutnik - 3 piny, 5V - silownik - 3 piny, - SWD - 3 piny lub 2 piny, - przycisk - 1 pin, - diody - 3 piny, - włącznik zasilania USB - 1 pin, 5v - USB - 2 piny, 5V - PC (PWR, LED+) - 2 piny, 5V - VCC,GND - 2 piny.
RED
GREEN
BLUE
VCC
GND
DUMMY
Sterowane zasilanie portu USB
Wylaczanie komputera
Programator SWD
Mostek H do siłownika liniowego z impulsatorem
Impulsator 48 zwarć na cal. Wymagany pull-up M_IMP.
Stabilizator 3.3V
Potrzebny pull-down
IN1 | IN2 0 0 HI 0 1 R 0 1 L 1 1 LO
MOLEX 12V
Uchwyt mocujący
IN L
IN R
OUT L
OUT R
Wzmacniacz głośnikowy
220uF zastąpione 1000uF przy wzmacniaczu

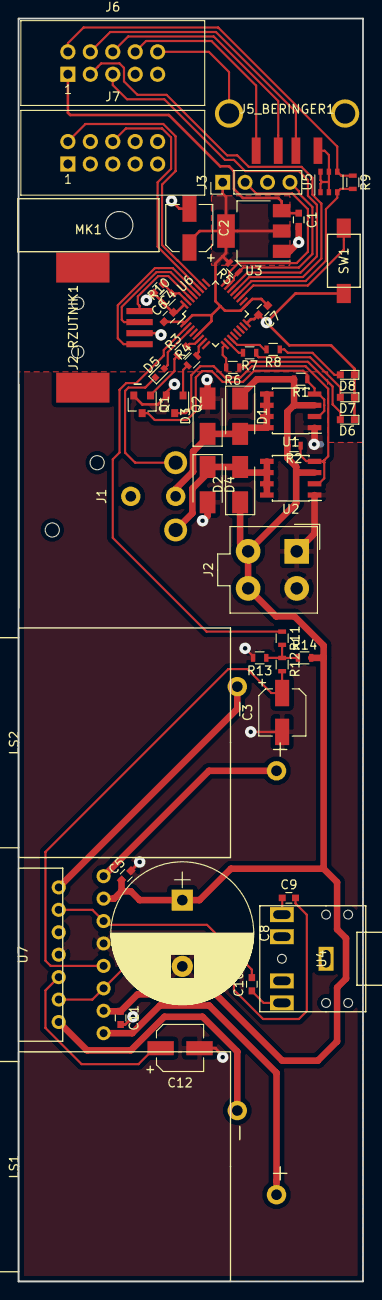
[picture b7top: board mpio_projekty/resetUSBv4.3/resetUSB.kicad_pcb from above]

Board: 2 copper layers, 39.0 x 143.0 mm, 54 parts (0 on the bottom side), 51 nets.
